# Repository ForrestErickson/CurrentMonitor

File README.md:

# Current Monitor
Connect in line with power supply to load and measure voltage drop across a selectable resistance.  
A project motivated in part to learn how to use JLCPCB to KiCAD plug-in.

# Online Viewer

* [Schematic Link](https://kicanvas.org/?github=https%3A%2F%2Fgithub.com%2FForrestErickson%2FCurrentMonitor%2Fblob%2Fmain%2FCurrentMonitor.kicad_sch)

* [PCB Link](https://kicanvas.org/?github=https%3A%2F%2Fgithub.com%2FForrestErickson%2FCurrentMonitor%2Fblob%2Fmain%2FCurrentMonitor.kicad_pcb)

## Credits  
JLC-Plugin-for-KiCad schematic symbol and PCB footprint and 3D model from:  https://github.com/Springer-Electronics/JLC2KiCad_lib  
JLC-Plugin-for-KiCad schematic Fabrication from:  https://github.com/bennymeg/JLC-Plugin-for-KiCad  
KiCad-DesignRules method from: https://github.com/labtroll/KiCad-DesignRules?tab=readme-ov-file  

## License and Warranty
License: This project and files are dedicated and released to the public domain.  
Warranty: This project and files are designed to kill you and render the earth uninhabitible, however they not guarenteed to do so.

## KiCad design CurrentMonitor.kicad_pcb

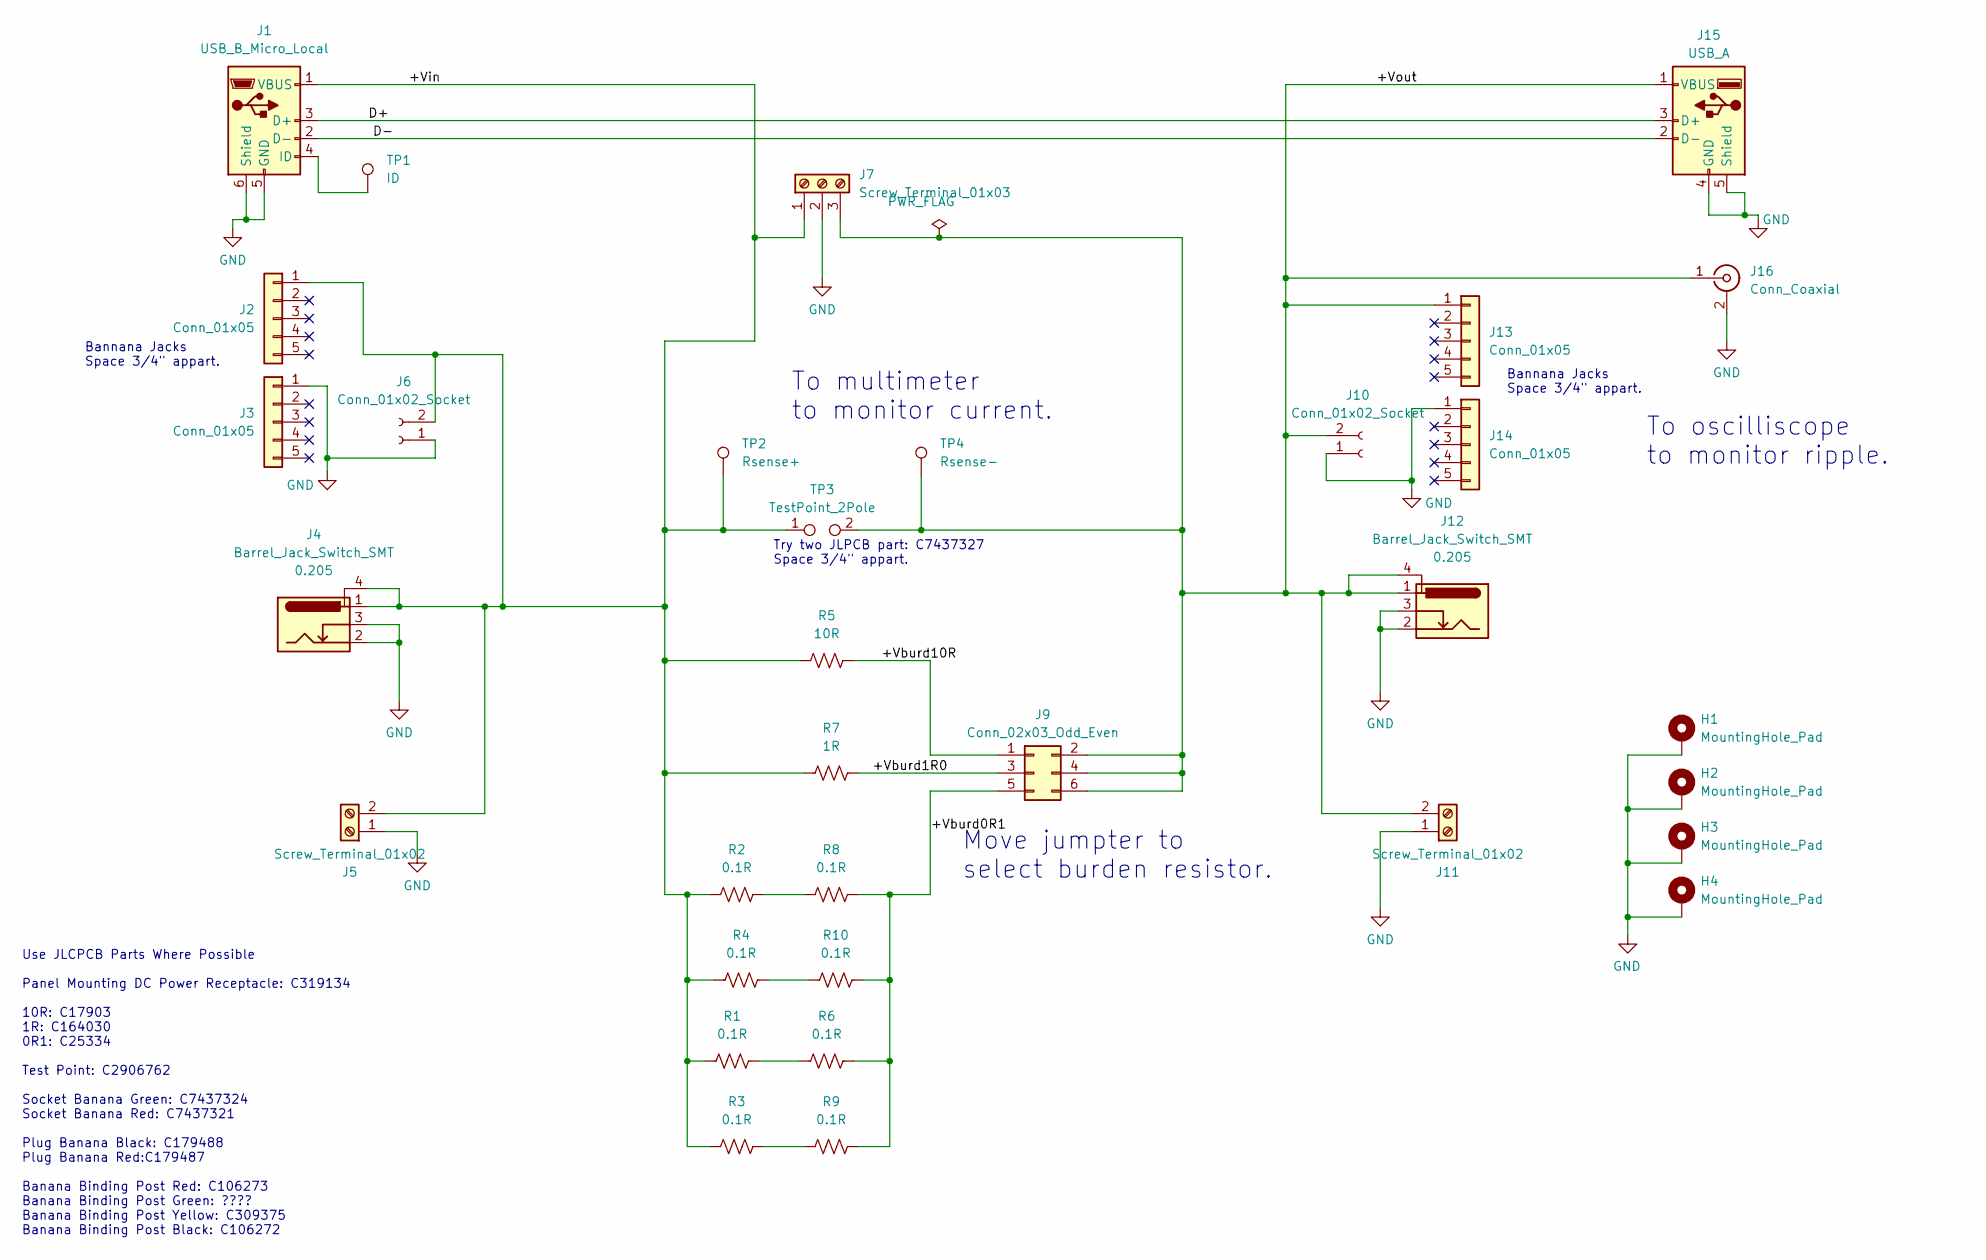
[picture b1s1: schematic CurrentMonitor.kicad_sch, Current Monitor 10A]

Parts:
H1, H2, H3, H4: MountingHole_Pad; MountingHole_3.5mm_Pad_Via
J1: USB_B_Micro_Local; USB_Micro-B_Amphenol_10118194_Horizontal
J2, J3, J13, J14: Conn_01x05; Banana_Cliff_FCR7350x_S16N-PC_Horizontal_5Pins
J4, J12: Barrel_Jack_Switch_SMT; BarrelJack_CLIFF_FC681465S_SMT_Horizontal; MPN DC-005-5A-2.0-SMT / 54-00164
J5, J11: Screw_Terminal_01x02; TerminalBlock_Phoenix_MKDS-1,5-2_1x02_P5.00mm_Horizontal
J6, J10: Conn_01x02_Socket; Banana_Jack_2Pin
J7: Screw_Terminal_01x03; TerminalBlock_Phoenix_MKDS-1,5-3_1x03_P5.00mm_Horizontal
J9: Conn_02x03_Odd_Even; PinHeader_2x03_P2.54mm_Vertical
J15: USB_A; USB_A_JLCPCB_C3038692_Horizontal
J16: Conn_Coaxial; BNC_Amphenol_B6252HB-NPP3G-50_Horizontal
R1, R2, R3, R4, R6, R8, R9, R10: 0.1R; R_1206_3216Metric_Pad1.30x1.75mm_HandSolder
R5: 10R; R_1206_3216Metric_Pad1.30x1.75mm_HandSolder
R7: 1R; R_1206_3216Metric_Pad1.30x1.75mm_HandSolder
TP1: ID; TestPoint_Loop_D2.50mm_Drill1.0mm
TP2: Rsense+; TestPoint_Loop_D2.50mm_Drill1.0mm
TP3: TestPoint_2Pole; Banana_Jack_2Pin
TP4: Rsense-; TestPoint_Loop_D2.50mm_Drill1.0mm

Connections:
/+Vburd0R1: J9.5, R6.2, R8.2, R9.2, R10.2
/+Vburd1R0: J9.3, R7.2
/+Vburd10R: J9.1, R5.2
/+Vin: J1.1 (VBUS), J2.1, J4.1, J4.4, J5.2, J6.2, J7.1, R1.1, R2.1, R3.1, R4.1, R5.1, R7.1, TP2.1, TP3.1
/+Vout: J7.3, J9.2, J9.4, J9.6, J10.2, J11.2, J12.1, J12.4, J13.1, J15.1 (VBUS), J16.1 (In), TP3.2, TP4.1
/D+: J1.3 (D+), J15.3 (D+)
/D-: J1.2 (D-), J15.2 (D-)
GND: H1.1, H2.1, H3.1, H4.1, J1.5 (GND), J1.6 (Shield), J3.1, J4.2, J4.3, J5.1, J6.1, J7.2, J10.1, J11.1, J12.2, J12.3, J14.1, J15.4 (GND), J15.5 (Shield), J16.2 (Ext)
unnamed: J1.4 (ID), TP1.1
unnamed: R1.2, R6.1
unnamed: R2.2, R8.1
unnamed: R3.2, R9.1
unnamed: R4.2, R10.1

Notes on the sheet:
Use JLCPCB Parts Where Possible Panel Mounting DC Power Receptacle: C319134 10R: C17903 1R: C164030 0R1: C25334 Test Point: C2906762 Socket Banana Green: C7437324 Socket Banana Red: C7437321 Plug Banana Black: C179488 Plug Banana Red:C179487 Banana Binding Post Red: C106273 Banana Binding Post Gree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
To multimeter to monitor current.
Try two JLPCB part: C7437327 Space 3/4" appart.
Bannana Jacks Space 3/4" appart.
Move jumpter to select burden resistor.
To oscilliscope to monitor ripple.

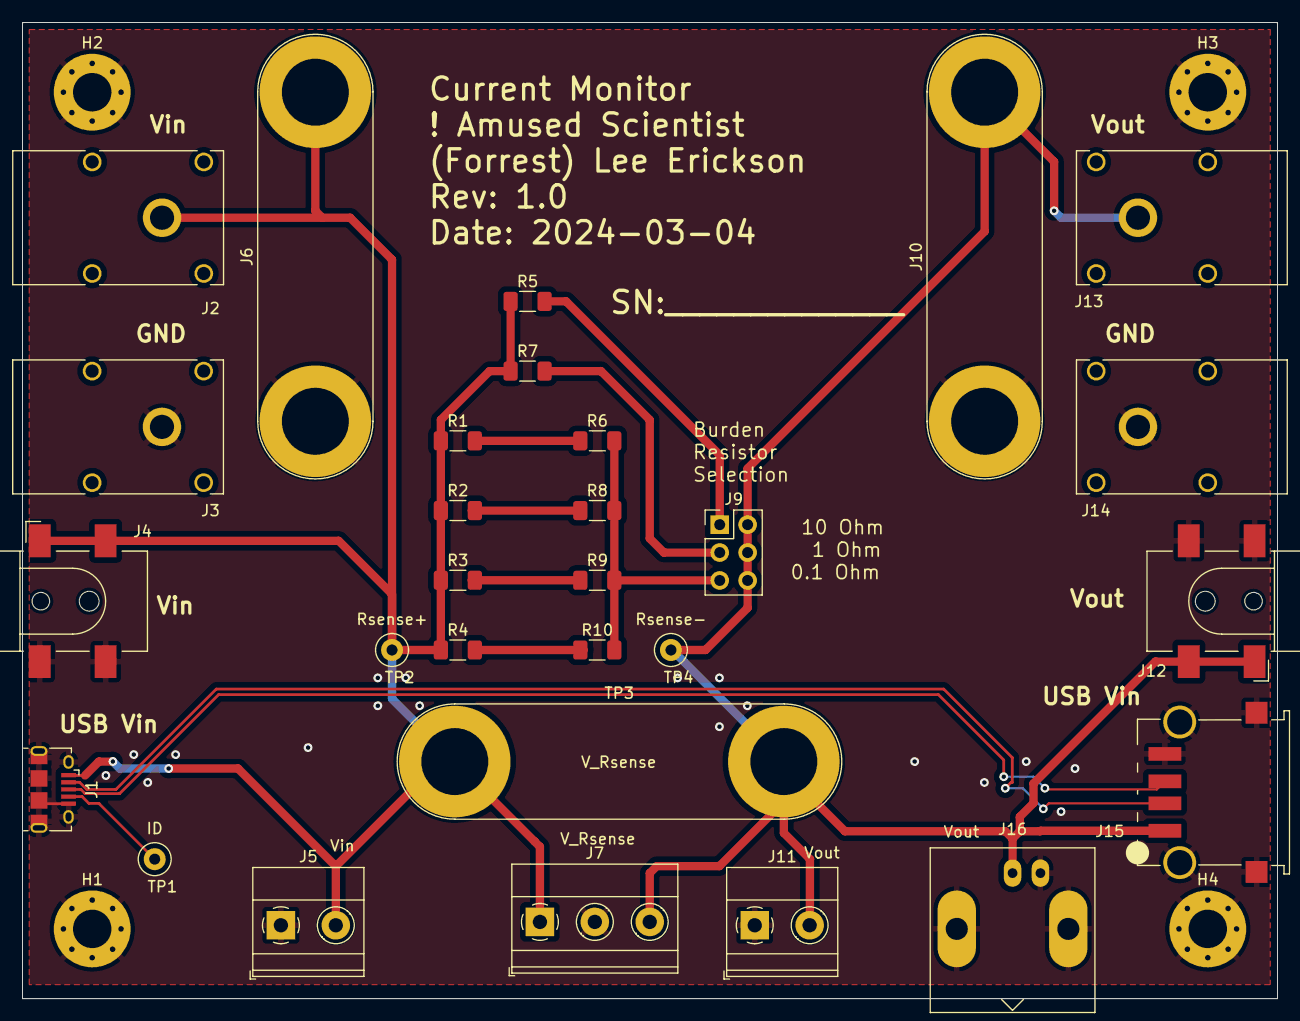
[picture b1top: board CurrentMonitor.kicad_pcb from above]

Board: 2 copper layers, 114.3 x 88.9 mm, 33 parts (0 on the bottom side), 13 nets.

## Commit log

2024-03-04 Initial commit.
2024-03-04 Add design rule check custom check.
2024-03-04 Add more JLCPCB parts, banana jacks and more.
2024-03-04 Create README.md
    Explain the project and project motiviation.
2024-03-04 Update README.md
    Add License and Warranty
2024-03-04 Update README.md
    Formatting only.
2024-03-04 Update README.md
    Add Credits
2024-03-04 Update README.md
    Format only.
2024-05-25 Add USB connectors, BNC for oscilliscope monitor.
2024-05-27 Initical placement of PCB components and edges. Still need USB parts.
2024-05-27 Add another bananna jack option. Get 3D foot prints working for Barrel Jack.
2024-07-09 Update with USB type A footprint. Update footprint of Barrel jack, mounting holes and bannana jacks. No ERC errors.
2024-07-10 Route copper on PCB.
2024-10-29 Update README.md
    Add to the README.md the KiCanvas links for Schematic and PCB.

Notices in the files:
CurrentMonitor.kicad_sch:
Release to Public Domain
